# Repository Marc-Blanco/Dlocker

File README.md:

## Dlocker

A funny looking and free and cool and asome and efficient and unconfined Ultimate E-READER DELUXE, for all the family granmas included!!
---------------
uses a waveshare screen multicolor for the display, cool!

|| 
|| 

||

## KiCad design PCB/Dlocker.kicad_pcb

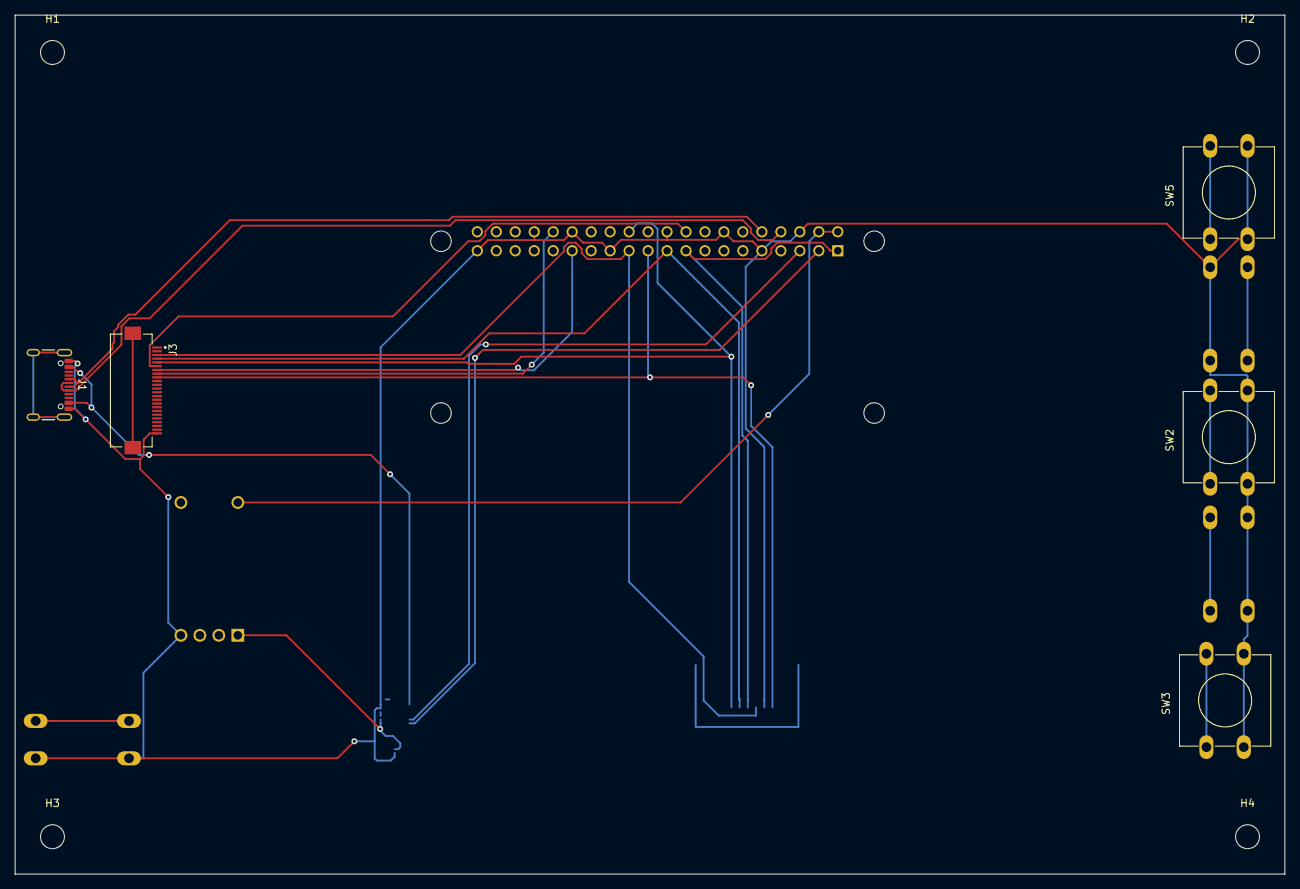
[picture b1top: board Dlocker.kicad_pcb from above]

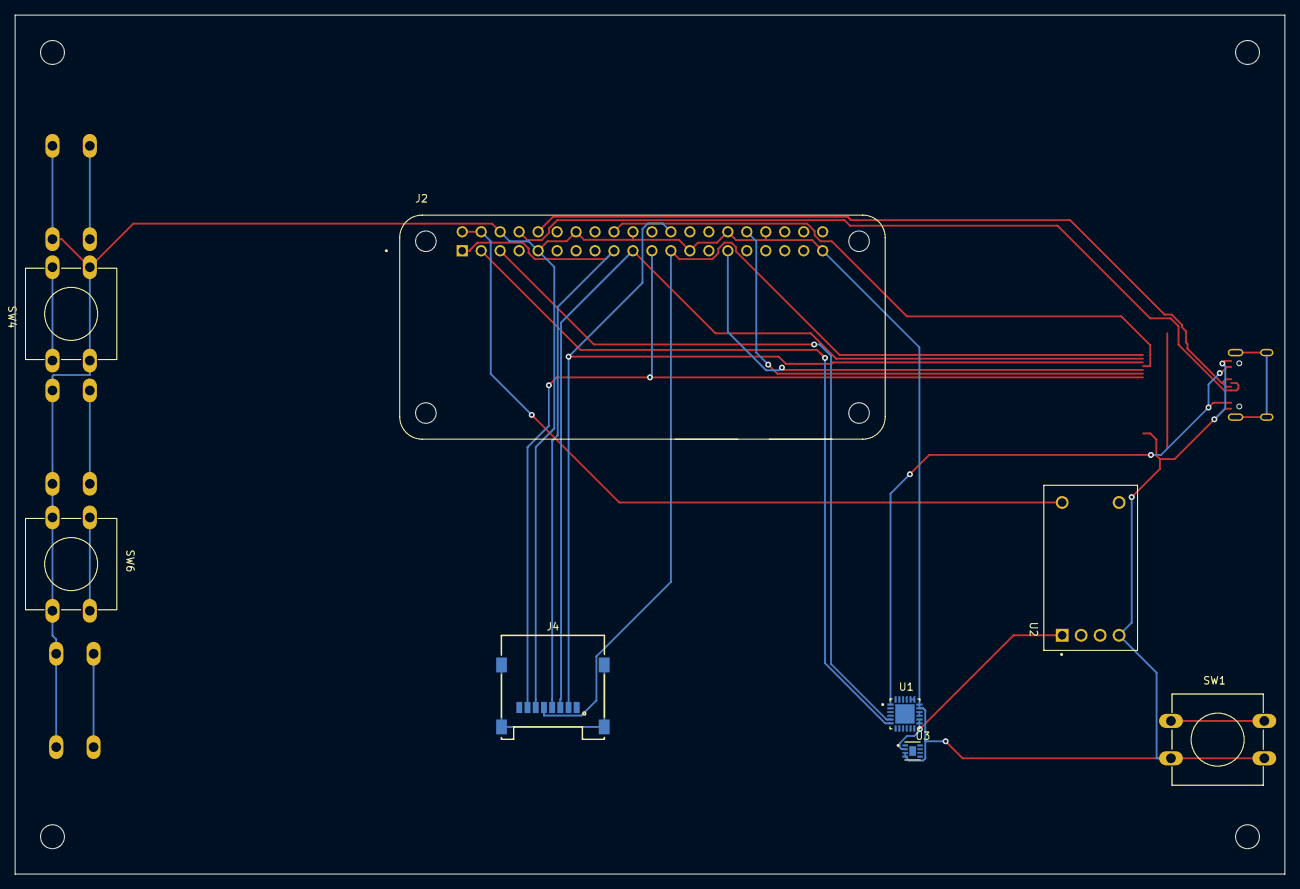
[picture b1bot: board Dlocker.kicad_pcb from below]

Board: 4 copper layers, 170.0 x 115.0 mm, 17 parts (8 on the bottom side), 20 nets.

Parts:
H1, H2, H3, H4: MountingHole_3.2mm; MountingHole_3.2mm_M3
J1: USB_C_Receptacle; USB_C_Receptacle_GCT_USB4105-xx-A_16P_TopMnt_Horizontal
J2: RASPBERRY_PI_ZERO_2_W; MODULE_RASPBERRY_PI_ZERO_2_W
J3: FH12-24S-0.5SH_55_; HRS_FH12-24S-0.5SH_55_
J4: 693072010801
SW1, SW2, SW3, SW4, SW5, SW6: SW_DPST_x2; SW_PUSH-12mm
U1: BQ25895RTWR; QFN50P400X400X80-25N
U2: RCD-24-0.60_Vref; CONV_RCD-24-0.60_Vref
U3: MAX17048G_T10; SON50P200X200X80-9N

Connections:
/DN: J1.A7 (D-), J1.B7 (D-), J2.10 (GPIO15/RXD0)
/EINK_BUSY: J2.32 (GPIO12), J3.8
/EINK_CS: J2.24 (GPIO8/SPI_~CE0), J3.5, J4.2 (CD/DAT3)
/EINK_DC: J2.18 (GPIO24/GPIO_GEN5), J3.6
/EINK_RST: J2.29 (GPIO5), J3.7
/I2C_SCL: J2.5 (GPIO3/SCL), U1.5 (SCL)
/I2C_SDA: J2.3 (GPIO2/SDA1), U1.6 (SDA)
/SPI_CLK: J2.23 (GPIO11/SPI_SCLK), J3.3, J4.5 (CLK)
/SPI_MISO: J2.21 (GPIO9/SPI_MISO), J3.9, J4.7 (DAT0)
/SPI_MOSI: J2.19 (GPIO10/SPI_MOSI), J3.4, J4.3 (CMD)
/USB_DP: J1.A6 (D+), J1.B6 (D+), J2.8 (GPIO14/TXD0)
/VBUS: J1.A4 (VBUS), J1.A9 (VBUS), J1.B4 (VBUS), J1.B9 (VBUS), U1.1 (VBUS)
/VCC: J2.2 (5V_2), J2.4 (5V_4), U2.6 (+VOUT)
/VDD: J2.1 (3V3_1), J2.17 (3V3_17), J4.4 (VDD)
BAT: U1.13 (BAT), U1.14 (BAT), U2.1 (+VIN), U3.2 (CELL)
GND: J1.A1 (GND), J1.A12 (GND), J1.B1 (GND), J1.B12 (GND), J2.6 (GND_6), J2.9 (GND_9), J2.14 (GND_14), J2.20 (GND_20), J2.25 (GND_25), J2.30 (GND_30), J2.34 (GND_34), J2.39 (GND_39), J3.24, J4.6 (VSS), SW1.2 (B), SW2.2 (B_2), SW3.2 (B), SW4.2 (B), SW5.2 (B), SW6.2 (B), U1.17 (PGND), U1.18 (PGND), U2.4 (GND), U3.3 (VDD), U3.4 (GND)
unnamed: J3.P1 (SHIELD), J3.P2 (SHIELD)
unnamed: J4.S1, J4.S2, J4.S3, J4.S4
SW: U1.19 (SW), U1.20 (SW)
SYS: U1.15 (SYS), U1.16 (SYS)
